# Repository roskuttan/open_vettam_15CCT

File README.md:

# open_vettam_15CCT

Tunable-white ceiling-light hardware project with a main control board and a
separate circular LED MCPCB.

## Current Hardware

### LED MCPCB

Verified from the current KiCad schematic and PCB:

- 130 mm circular board routed on `F.Cu`.
- 84 LEDs: 42 x `L128-5090HA35000K1` cool-white 5000 K and
  42 x `L128-3090HA35000K1` warm-white 3000 K.
- Six CW strings and six WW strings, each with a `6.8 ohm` resistor.
- LED power pads are `CW+`, `WW+`, and one shared `LED-`.
- The shared `LED-` pad connects to `GND0` used by both LED sheets.
- The three LED power wire pads are `3 x 6 mm`. The previous four separate
  power pads were `5 x 10 mm`.
- A `TMP112AIDRLR` temperature sensor is connected through `TEMP_3V3`,
  `TEMP_GND`, `TEMP_SCL`, and `TEMP_SDA` pads.

Sources:

- [`hardware/led-mcpcb/kicad/led_mcpcb.kicad_sch`](hardware/led-mcpcb/kicad/led_mcpcb.kicad_sch)
- [`hardware/led-mcpcb/kicad/led_mcpcb.kicad_pcb`](hardware/led-mcpcb/kicad/led_mcpcb.kicad_pcb)
- [`hardware/led-mcpcb/kicad/CW-5000.kicad_sch`](hardware/led-mcpcb/kicad/CW-5000.kicad_sch)
- [`hardware/led-mcpcb/kicad/WW-3000.kicad_sch`](hardware/led-mcpcb/kicad/WW-3000.kicad_sch)

### Main Board

Verified from the current KiCad schematic and PCB:

- 68.25 x 49 mm, two copper layers, fully routed.
- `24V` input with an `LMR51610YDBVR` buck regulator producing `3V3`.
- `ESP32-C6-MINI-1-N4` controller module.
- Two `TPS922053DRRR` LED drivers controlled by `PWM_CW` and `PWM_WW`.
- `LED_OUT` connector `J3` pinout:

| Pin | Current net |
|---:|---|
| 1 | `+24V` |
| 2 | `WW-` |
| 3 | `+24V` |
| 4 | `CW-` |

- `TEMP_IN` connector `J5` pinout:

| Pin | Current net |
|---:|---|
| 1 | `+3V3` |
| 2 | `GND` |
| 3 | `SCL` |
| 4 | `SDA` |

Sources:

- [`hardware/main-board/kicad/open_vettam_15CCT.kicad_sch`](hardware/main-board/kicad/open_vettam_15CCT.kicad_sch)
- [`hardware/main-board/kicad/open_vettam_15CCT.kicad_pcb`](hardware/main-board/kicad/open_vettam_15CCT.kicad_pcb)
- [`hardware/main-board/kicad/24v_Input.kicad_sch`](hardware/main-board/kicad/24v_Input.kicad_sch)
- [`hardware/main-board/kicad/24-5_buck.kicad_sch`](hardware/main-board/kicad/24-5_buck.kicad_sch)
- [`hardware/main-board/kicad/MCU.kicad_sch`](hardware/main-board/kicad/MCU.kicad_sch)
- [`hardware/main-board/kicad/cc_driver.kicad_sch`](hardware/main-board/kicad/cc_driver.kicad_sch)

## Interface Status

The current board files do not have matching LED power interfaces:

- The LED MCPCB uses `CW+`, `WW+`, and shared `LED-`.
- The main board still outputs `+24V`, `WW-`, `+24V`, and `CW-`.

The main-board LED-driver section must be revised before it can connect directly
to the current LED MCPCB interface.

## Repository Layout

```text
hardware/
  main-board/
    kicad/          Main-board KiCad source
    bom/            Main-board BOM export
    manufacturing/  Gerber ZIP, netlist, and stencil DXF files
  led-mcpcb/
    kicad/          LED-board KiCad source
    manufacturing/  LED-board stencil DXF
firmware/
  esp32-c6/         Firmware placeholder; no source code is present yet
docs/               Datasheets and manufacturing notes
cad/                Enclosure CAD
mechanical/         Mechanical models and assembly assets
```

Matter over Thread, CW/WW PWM, brightness control, and color-temperature control
are listed as planned firmware scope in
[`firmware/esp32-c6/README.md`](firmware/esp32-c6/README.md); they are not
implemented in this repository yet.

## License

- Hardware and CAD source: CERN-OHL-P-2.0
- Firmware and scripts: MIT
- Documentation and media: not licensed unless stated otherwise

See [`LICENSE`](LICENSE) and [`LICENSES/`](LICENSES/).

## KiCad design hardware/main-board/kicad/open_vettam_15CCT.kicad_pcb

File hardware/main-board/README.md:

# Main Board

Main ESP32-C6 control board.

- `kicad/`: KiCad schematic and PCB source
- `bom/`: BOM exports
- `manufacturing/`: fabrication, stencil, and netlist outputs

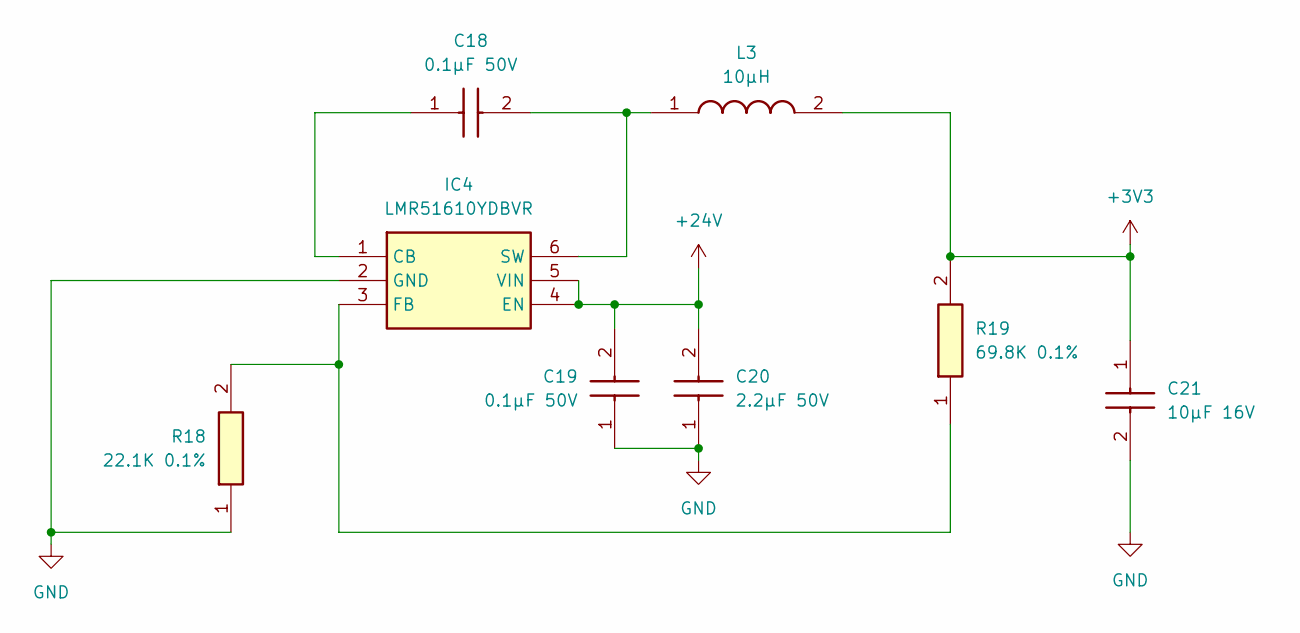
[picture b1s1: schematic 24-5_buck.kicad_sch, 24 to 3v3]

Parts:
C18, C19: 0.1µF 50V; CAPC1608X90N; Manufacturer_Part_Number CL10B104KB8NNNL; Mouser Part Number 187-CL10B104KB8NNNL
C20: 2.2µF 50V; CAPC3225X270N; Manufacturer_Part_Number CL32B225KBJNNNE; Mouser Part Number 187-CL32B225KBJNNNE
C21: 10µF 16V; CAPC3216X180N; Manufacturer_Part_Number C3216X7R1C106K160AC; Mouser Part Number 810-C3216X7R1C106K
IC4: LMR51610YDBVR; SOT95P280X145-6N; Manufacturer_Part_Number LMR51610YDBVR; Mouser Part Number 595-LMR51610YDBVR
L3: 10µH; SRP5030HMT2R2M; Manufacturer_Part_Number SRP5030HMT-100M; Mouser Part Number 652-SRP5030HMT-100M
R18: 22.1K 0.1%; ERA3AEB101V; Manufacturer_Part_Number ERA-3AEB2212V; Mouser Part Number 667-ERA-3AEB2212V
R19: 69.8K 0.1%; ERA3AEB101V; Manufacturer_Part_Number ERA-3AEB6982V; Mouser Part Number 667-ERA-3AEB6982V

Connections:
+3V3: C21.1, L3.2, R19.2; also elsewhere on the board
+24V: C19.2, C20.2, IC4.4 (EN), IC4.5 (VIN); also elsewhere on the board
GND: C19.1, C20.1, C21.2, IC4.2 (GND), R18.1; also elsewhere on the board
unnamed: C18.1, IC4.1 (CB)
unnamed: IC4.3 (FB), R18.2, R19.1
unnamed: C18.2, IC4.6 (SW), L3.1

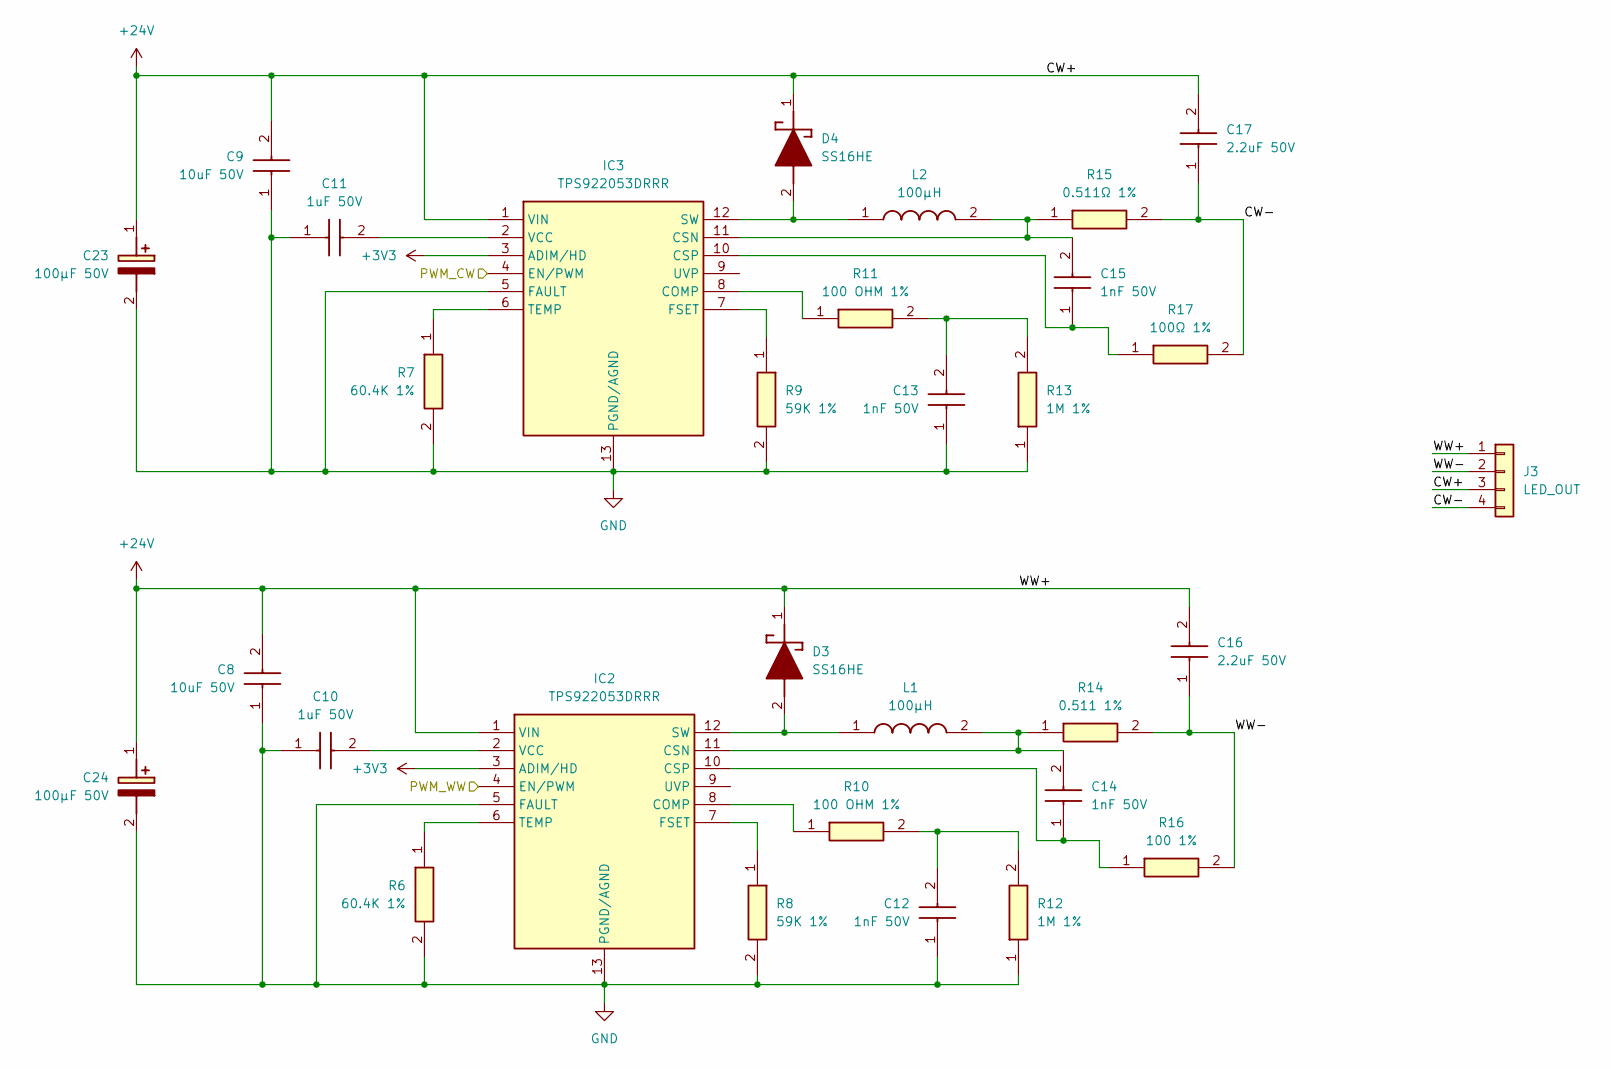
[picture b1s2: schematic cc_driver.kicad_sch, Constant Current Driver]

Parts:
C8, C9: 10uF 50V; CAPC3216X180N; Manufacturer_Part_Number CL31B106KBHNNNE; Mouser Part Number 187-CL31B106KBHNNNE
C10, C11: 1uF 50V; CAPC1608X95N; Manufacturer_Part_Number UMK107AB7105KA-T; Mouser Part Number 963-UMK107AB7105KA-T
C12, C13, C14, C15: 1nF 50V; CAPC1608X90N; Manufacturer_Part_Number CL10B102KB8NNNC; Mouser Part Number 187-CL10B102KB8NNNC
C16, C17: 2.2uF 50V; CAPC3216X180N; Manufacturer_Part_Number CL31B225KBHNNNE; Mouser Part Number 187-CL31B225KBHNNNE
C23, C24: 100µF 50V; CAPAE1030X1050N; Manufacturer_Part_Number 50THV100M10X10.5; Mouser Part Number 232-50THV100M10X10.5
D3, D4: SS16HE; Manufacturer_Part_Number SS16HE; Mouser Part Number 512-SS16HE
IC2, IC3: TPS922053DRRR; SON50P300X300X80-13N-D; Manufacturer_Part_Number TPS922053DRRR; Mouser Part Number 595-TPS922053DRRR
J3: LED_OUT; SolderWire-0.25sqmm_1x04_P4.5mm_D0.65mm_OD2mm
L1, L2: 100µH; AMDLA1004S101MT; Manufacturer_Part_Number AMDLA1004S-101MT; Mouser Part Number 815-AMDLA1004S-101MT
R6, R7: 60.4K 1%; RESC1608X55N; Manufacturer_Part_Number RC0603FR-0760K4L; Mouser Part Number 603-RC0603FR-0760K4L
R8, R9: 59K 1%; RESC1608X55N; Manufacturer_Part_Number RC0603FR-0759KL; Mouser Part Number 603-RC0603FR-0759KL
R10, R11: 100 OHM 1%; RESC1608X55N; Manufacturer_Part_Number RC0603FR-07100RL; Mouser Part Number 603-RC0603FR-07100RL
R12, R13: 1M 1%; RESC1608X55N; Manufacturer_Part_Number RC0603FR-071ML; Mouser Part Number 603-RC0603FR-071ML
R14: 0.511 1%; RESC3216X70N; Manufacturer_Part_Number SR732BTTDR511F; Mouser Part Number 660-SR732BTTER511F
R15: 0.511Ω 1%; RESC3216X70N; Manufacturer_Part_Number SR732BTTDR511F; Mouser Part Number 660-SR732BTTER511F
R16: 100 1%; RESC1608X55N; Manufacturer_Part_Number RC0603FR-07100RL; Mouser Part Number 603-RC0603FR-07100RL
R17: 100Ω 1%; RESC1608X55N; Manufacturer_Part_Number RC0603FR-07100RL; Mouser Part Number 603-RC0603FR-07100RL

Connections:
+3V3: IC2.3 (ADIM/HD), IC3.3 (ADIM/HD); also elsewhere on the board
+24V: C8.2, C9.2, C16.2, C17.2, C23.1 (+), C24.1 (+), D3.1 (K), D4.1 (K), IC2.1 (VIN), IC3.1 (VIN), J3.1, J3.3; also elsewhere on the board
/CC_Driver/CW-: C17.1, J3.4, R15.2, R17.2
/CC_Driver/PWM_CW: IC3.4 (EN/PWM); also elsewhere on the board
/CC_Driver/PWM_WW: IC2.4 (EN/PWM); also elsewhere on the board
/CC_Driver/WW-: C16.1, J3.2, R14.2, R16.2
GND: C8.1, C9.1, C10.1, C11.1, C12.1, C13.1, C23.2 (-), C24.2 (-), IC2.5 (FAULT), IC2.13 (PGND/AGND), IC3.5 (FAULT), IC3.13 (PGND/AGND), R6.2, R7.2, R8.2, R9.2, R12.1, R13.1; also elsewhere on the board
unnamed: C12.2, R10.2, R12.2
unnamed: C13.2, R11.2, R13.2
unnamed: D3.2 (A), IC2.12 (SW), L1.1
unnamed: D4.2 (A), IC3.12 (SW), L2.1
unnamed: IC2.8 (COMP), R10.1
unnamed: C14.2, IC2.11 (CSN), L1.2, R14.1
unnamed: C14.1, IC2.10 (CSP), R16.1
unnamed: IC2.7 (FSET), R8.1
unnamed: IC2.6 (TEMP), R6.1
unnamed: C10.2, IC2.2 (VCC)
unnamed: IC3.8 (COMP), R11.1
unnamed: C15.2, IC3.11 (CSN), L2.2, R15.1
unnamed: C15.1, IC3.10 (CSP), R17.1
unnamed: IC3.7 (FSET), R9.1
unnamed: IC3.6 (TEMP), R7.1
unnamed: C11.2, IC3.2 (VCC)

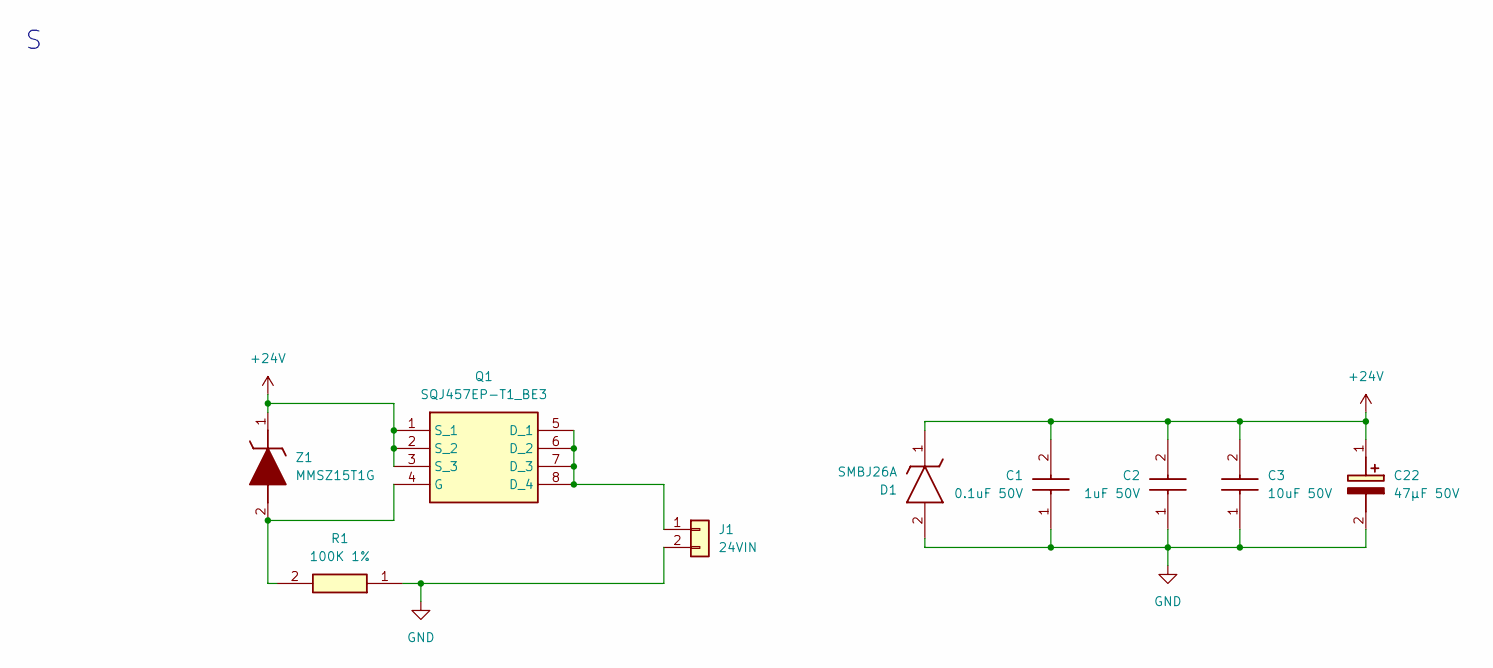
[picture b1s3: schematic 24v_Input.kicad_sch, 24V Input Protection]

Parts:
C1: 0.1uF 50V; CAPC1608X90N; Manufacturer_Part_Number CL10B104KB8NNWC; Mouser Part Number 187-CL10B104KB8NNWC
C2: 1uF 50V; CAPC1608X95N; Manufacturer_Part_Number UMK107AB7105KA-T; Mouser Part Number 963-UMK107AB7105KA-T
C3: 10uF 50V; CAPC3216X180N; Manufacturer_Part_Number CL31B106KBHNNNE; Mouser Part Number 187-CL31B106KBHNNNE
C22: 47µF 50V; CAPAE830X1050N; Manufacturer_Part_Number HHXC500ARA470MHA0G; Mouser Part Number 661-HHXC500A470MHA0G
D1: SMBJ26A; DIOM5436X261N; Manufacturer_Part_Number SMBJ26A; Mouser Part Number 576-SMBJ26A
J1: 24VIN; SolderWire-0.15sqmm_1x06_P4mm_D0.5mm_OD1.5mm
Q1: SQJ457EP-T1_BE3; SQJ416EPT1_GE3; Manufacturer_Part_Number SQJ457EP-T1_BE3; Mouser Part Number 78-SQJ457EP-T1_BE3
R1: 100K 1%; RESC1608X55N; Manufacturer_Part_Number RC0603FR-07100KL; Mouser Part Number 603-RC0603FR-07100KL
Z1: MMSZ15T1G; DIOM3716X135N; Manufacturer_Part_Number MMSZ15T1G; Mouser Part Number 863-MMSZ15T1G

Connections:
+24V: C1.2, C2.2, C3.2, C22.1 (+), D1.1 (K), Q1.1 (S_1), Q1.2 (S_2), Q1.3 (S_3), Z1.1 (K); also elsewhere on the board
GND: C1.1, C2.1, C3.1, C22.2 (-), D1.2 (A), J1.2, R1.1; also elsewhere on the board
unnamed: J1.1, Q1.5 (D_1), Q1.6 (D_2), Q1.7 (D_3), Q1.8 (D_4)
unnamed: Q1.4 (G), R1.2, Z1.2 (A)

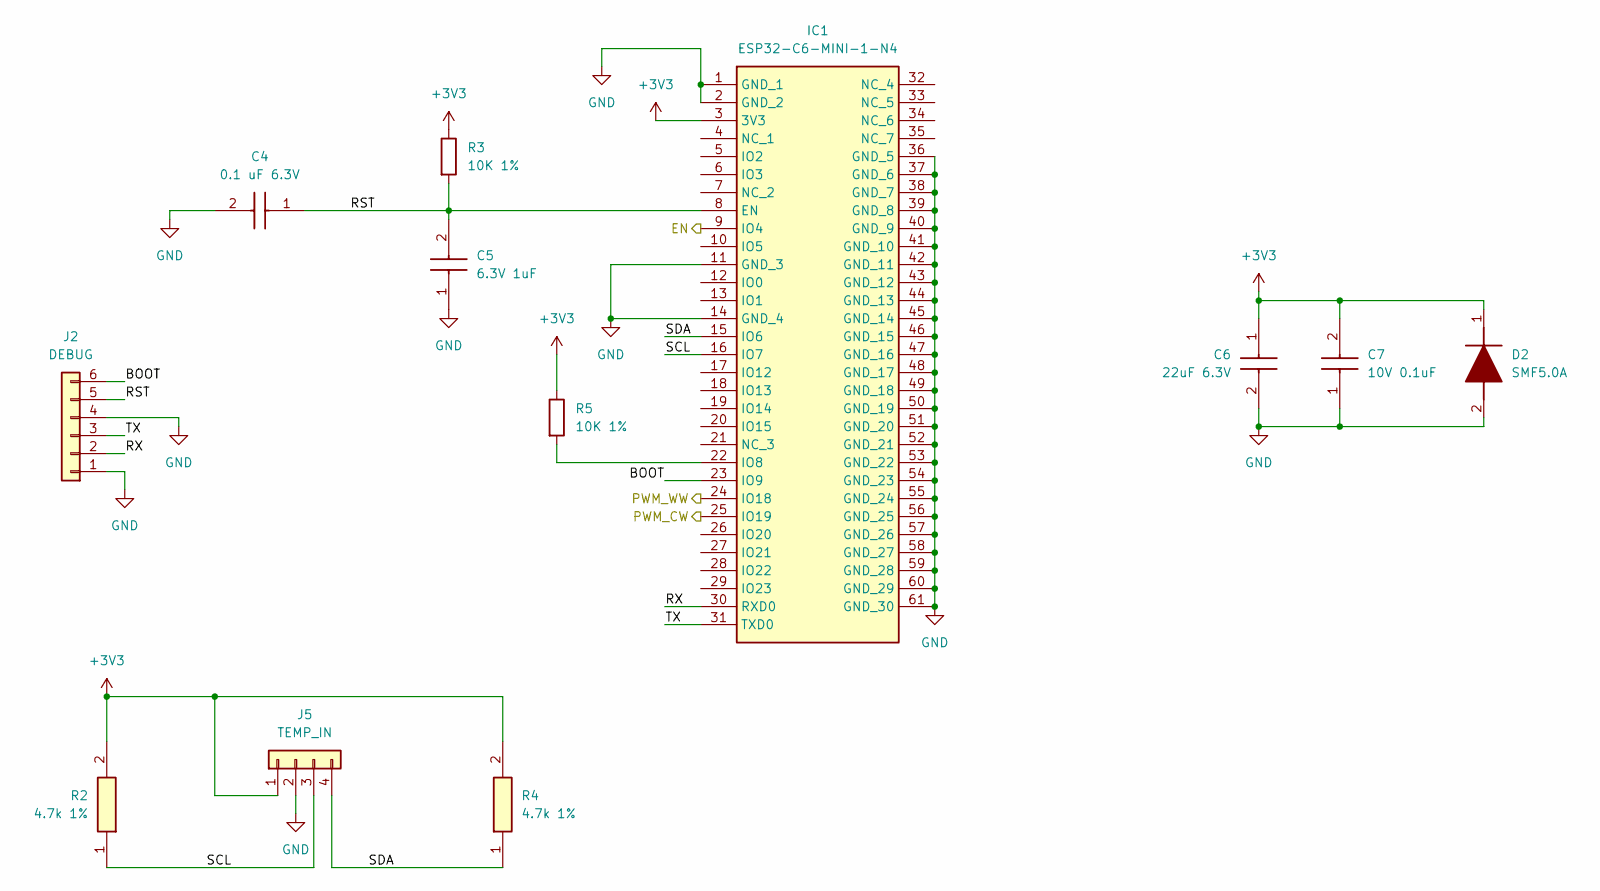
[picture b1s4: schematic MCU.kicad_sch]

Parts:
C4: 0.1 uF 6.3V; C0603; Manufacturer_Part_Number C0603C104K9PACTU; Mouser Part Number 80-C0603C104K9P
C5: 6.3V 1uF; CAPC1608X90N; Manufacturer_Part_Number CL10B105KQ8NNNC; Mouser Part Number 187-CL10B105KQ8NNNC
C6: 22uF 6.3V; CAPC1608X100N; Manufacturer_Part_Number CL10A226MQ8NRNE; Mouser Part Number 187-CL10A226MQ8NRNE
C7: 10V 0.1uF; C0402; Manufacturer_Part_Number C0402C104K8RACAUTO; Mouser Part Number 80-C0402C104K8RAUTO
D2: SMF5.0A; SODFL3618X110N; Manufacturer_Part_Number SMF5.0A; Mouser Part Number 576-SMF5.0A
IC1: ESP32-C6-MINI-1-N4; ESP32C6MINI1N4; Manufacturer_Part_Number ESP32-C6-MINI-1-N4; Mouser Part Number 356-ESP32C6MINI-1-N4
J2: DEBUG; SolderWire-0.15sqmm_1x06_P4mm_D0.5mm_OD1.5mm
J5: TEMP_IN; SolderWire-0.15sqmm_1x04_P4mm_D0.5mm_OD1.5mm
R2, R4: 4.7k 1%; RESC1608X55N; Manufacturer_Part_Number ERJ-3EKF4701V; Mouser Part Number 667-ERJ-3EKF4701V
R3, R5: 10K 1%; R_0603_1608Metric_Pad0.98x0.95mm_HandSolder; Manufacturer_Part_Number RC0603FR-0710KL; Mouser Part Number 603-RC0603FR-0710KL

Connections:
+3V3: C6.1, C7.2, D2.1 (K), IC1.3 (3V3), J5.1, R2.2, R3.1, R4.2, R5.1; also elsewhere on the board
/MCU/<NO NET>: IC1.23 (IO9), J2.6; also elsewhere on the board
/MCU/RST: C4.1, C5.2, IC1.8 (EN), J2.5, R3.2; also elsewhere on the board
/MCU/RX: IC1.30 (RXD0), J2.2; also elsewhere on the board
/MCU/SCL: IC1.16 (IO7), J5.3, R2.1; also elsewhere on the board
/MCU/SDA: IC1.15 (IO6), J5.4, R4.1; also elsewhere on the board
/MCU/TX: IC1.31 (TXD0), J2.3; also elsewhere on the board
GND: C4.2, C5.1, C6.2, C7.1, D2.2 (A), IC1.1 (GND_1), IC1.2 (GND_2), IC1.11 (GND_3), IC1.14 (GND_4), IC1.36 (GND_5), IC1.37 (GND_6), IC1.38 (GND_7), IC1.39 (GND_8), IC1.40 (GND_9), IC1.41 (GND_10), IC1.42 (GND_11), IC1.43 (GND_12), IC1.44 (GND_13), IC1.45 (GND_14), IC1.46 (GND_15), IC1.47 (GND_16), IC1.48 (GND_17), IC1.49 (GND_18), IC1.50 (GND_19), IC1.51 (GND_20), IC1.52 (GND_21), IC1.53 (GND_22), IC1.54 (GND_23), IC1.55 (GND_24), IC1.56 (GND_25), IC1.57 (GND_26), IC1.58 (GND_27), IC1.59 (GND_28), IC1.60 (GND_29), IC1.61 (GND_30), J2.1, J2.4, J5.2; also elsewhere on the board
unnamed 18: IC1.22 (IO8), R5.2; also elsewhere on the board

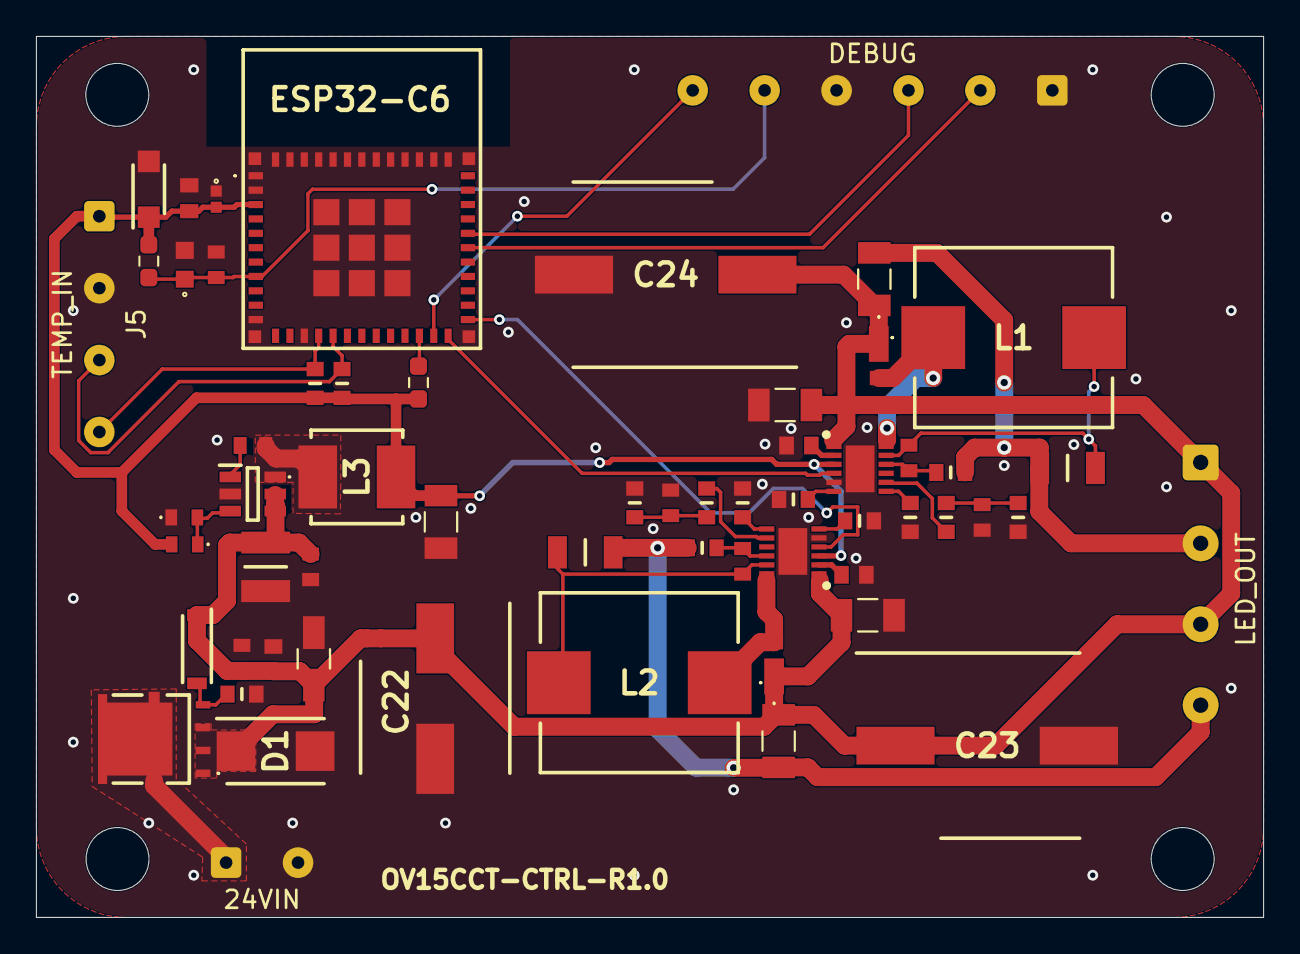
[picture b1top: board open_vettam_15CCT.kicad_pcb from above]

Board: 2 copper layers, 68.2 x 49.0 mm, 60 parts (0 on the bottom side), 35 nets.

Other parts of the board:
ESP32-C6: ESP32-C6-MINI-1-N4; ESP32C6MINI1N4

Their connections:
+3V3: ESP32-C6.3 (3V3); also elsewhere on the board
/CC_Driver/PWM_CW: ESP32-C6.25 (IO19); also elsewhere on the board
/CC_Driver/PWM_WW: ESP32-C6.24 (IO18); also elsewhere on the board
/MCU/<NO NET>: ESP32-C6.23 (IO9); also elsewhere on the board
/MCU/RST: ESP32-C6.8 (EN); also elsewhere on the board
/MCU/RX: ESP32-C6.30 (RXD0); also elsewhere on the board
/MCU/SCL: ESP32-C6.16 (IO7); also elsewhere on the board
/MCU/SDA: ESP32-C6.15 (IO6); also elsewhere on the board
/MCU/TX: ESP32-C6.31 (TXD0); also elsewhere on the board
GND: ESP32-C6.1 (GND_1), ESP32-C6.2 (GND_2), ESP32-C6.11 (GND_3), ESP32-C6.14 (GND_4), ESP32-C6.36 (GND_5), ESP32-C6.37 (GND_6), ESP32-C6.38 (GND_7), ESP32-C6.39 (GND_8), ESP32-C6.40 (GND_9), ESP32-C6.41 (GND_10), ESP32-C6.42 (GND_11), ESP32-C6.43 (GND_12), ESP32-C6.44 (GND_13), ESP32-C6.45 (GND_14), ESP32-C6.46 (GND_15), ESP32-C6.47 (GND_16), ESP32-C6.48 (GND_17), ESP32-C6.49 (GND_18), ESP32-C6.50 (GND_19), ESP32-C6.51 (GND_20), ESP32-C6.52 (GND_21), ESP32-C6.53 (GND_22), ESP32-C6.54 (GND_23), ESP32-C6.55 (GND_24), ESP32-C6.56 (GND_25), ESP32-C6.57 (GND_26), ESP32-C6.58 (GND_27), ESP32-C6.59 (GND_28), ESP32-C6.60 (GND_29), ESP32-C6.61 (GND_30); also elsewhere on the board
unnamed 18: ESP32-C6.22 (IO8); also elsewhere on the board

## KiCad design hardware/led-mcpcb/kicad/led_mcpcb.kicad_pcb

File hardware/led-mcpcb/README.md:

# LED MCPCB

Metal-core LED board for the CW and WW LED strings.

- `kicad/`: KiCad schematic, PCB, and design rules
- `tools/`: placement helper files

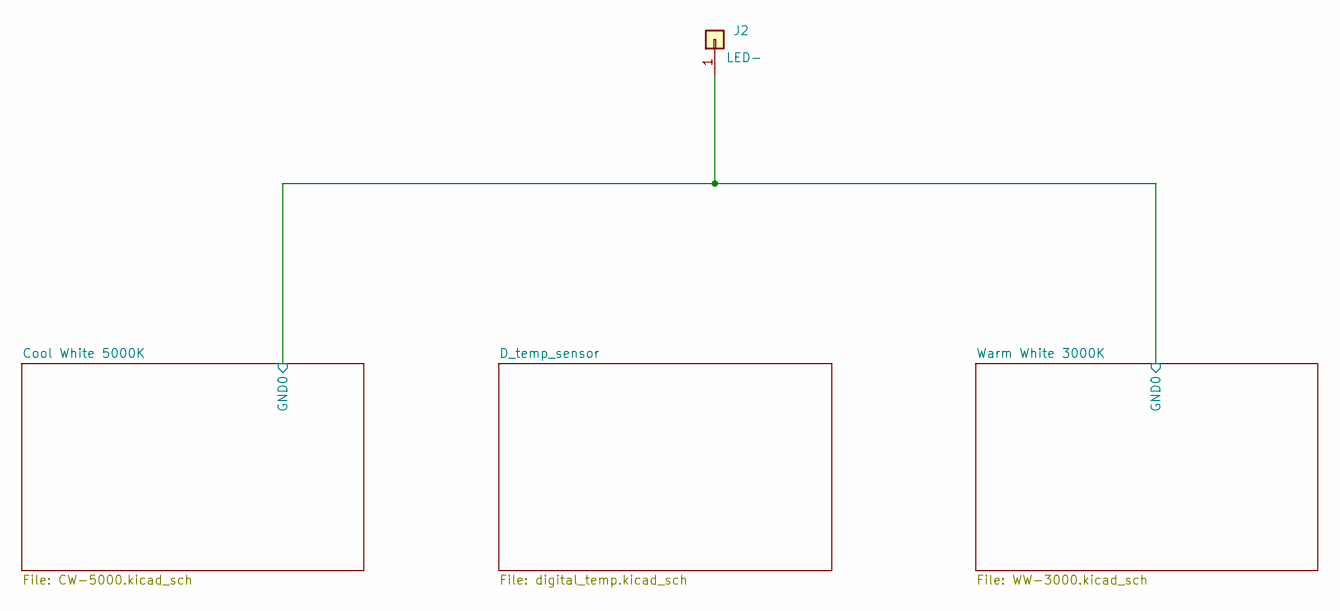
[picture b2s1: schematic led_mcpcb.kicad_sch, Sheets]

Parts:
J2: LED-; SolderWirePad_1x01_SMD_3x6mm

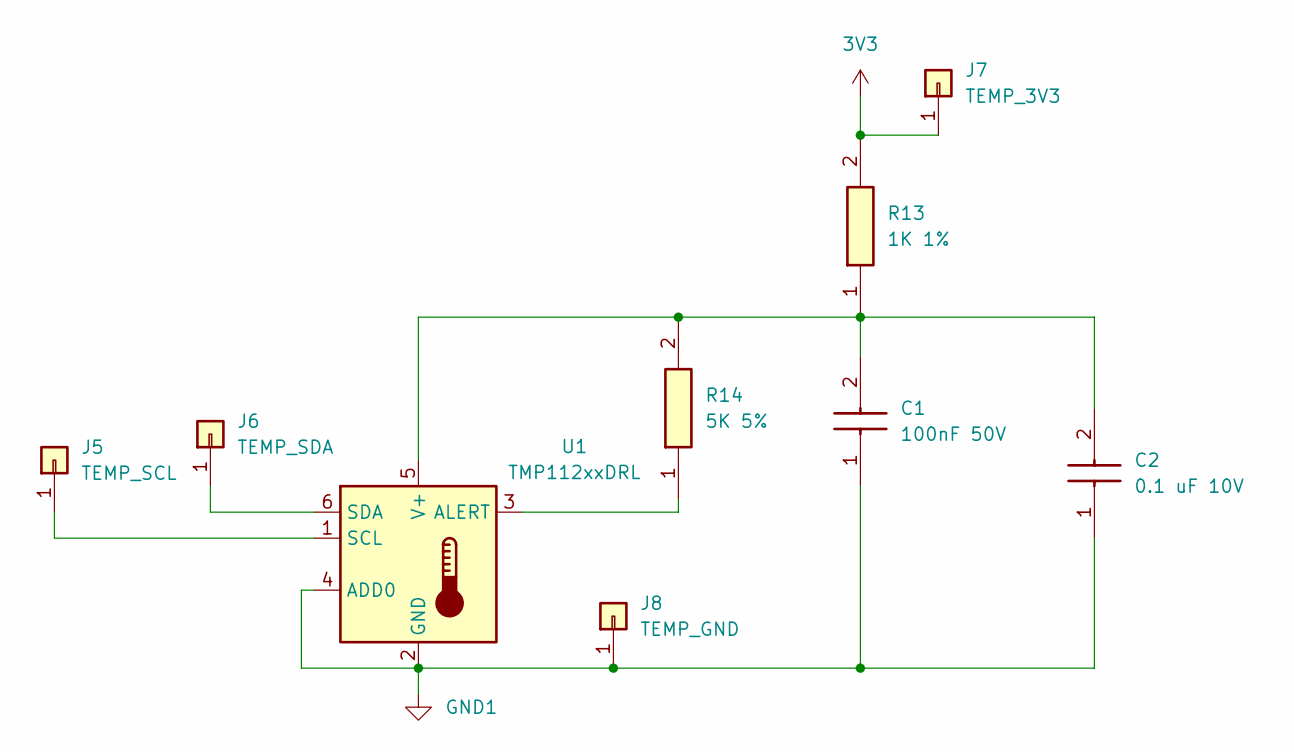
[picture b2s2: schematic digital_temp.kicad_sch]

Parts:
C1: 100nF 50V; CAPC1608X90N; Manufacturer_Part_Number CL10B104KB8NNNL; Mouser Part Number 187-CL10B104KB8NNNL
C2: 0.1 uF 10V; C0402; Manufacturer_Part_Number C0402C104K8RACAUTO; Mouser Part Number 80-C0402C104K8RAUTO
J5: TEMP_SCL; SolderWirePad_1x01_SMD_1x2mm
J6: TEMP_SDA; SolderWirePad_1x01_SMD_1x2mm
J7: TEMP_3V3; SolderWirePad_1x01_SMD_1x2mm
J8: TEMP_GND; SolderWirePad_1x01_SMD_1x2mm
R13: 1K 1%; RESC1608X55N; Manufacturer_Part_Number ERJ-3EKF1001V; Mouser Part Number 667-ERJ-3EKF1001V
R14: 5K 5%; RESC2012X50N; Manufacturer_Part_Number CRCW08055K00JNTA; Mouser Part Number 71-CRCW0805J-5K
U1: TMP112xxDRL; SOT-563; Manufacturer_Part_Number TMP112AIDRLR; Mouser Part Number 595-TMP112AIDRLR

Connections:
3V3: J7.1 (Pin_1_1), R13.2
GND1: C1.1, C2.1, J8.1 (Pin_1_1), U1.2 (GND), U1.4 (ADD0)
unnamed: J5.1 (Pin_1_1), U1.1 (SCL)
unnamed: J6.1 (Pin_1_1), U1.6 (SDA)
unnamed: R14.1, U1.3 (ALERT)
unnamed: C1.2, C2.2, R13.1, R14.2, U1.5 (V+)

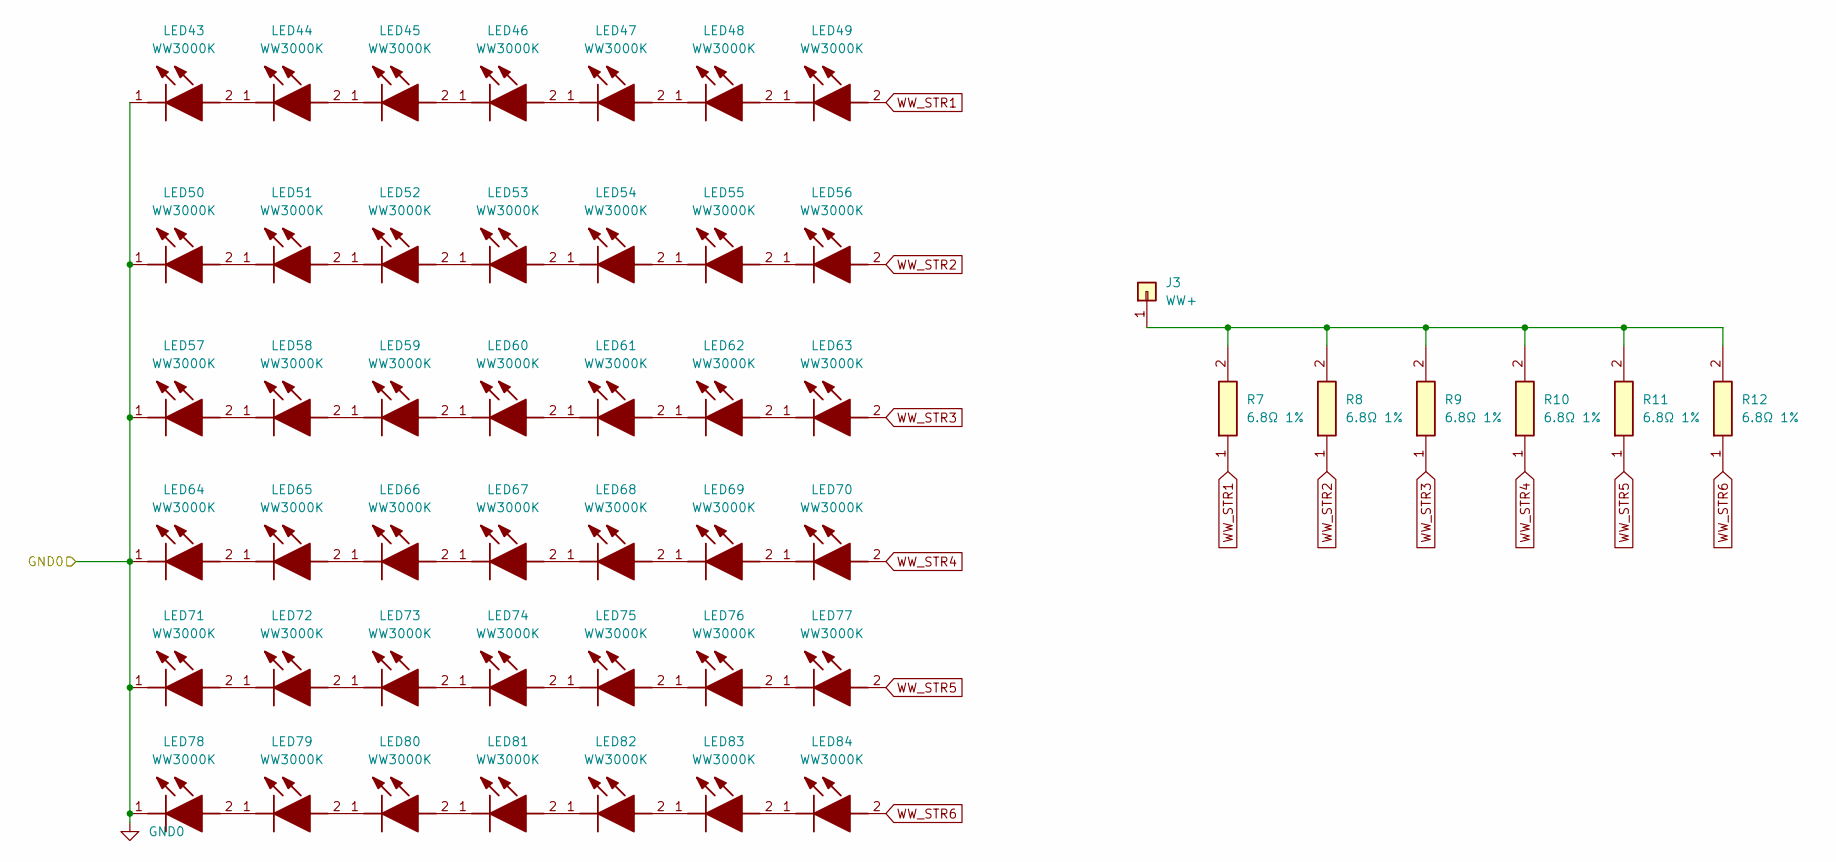
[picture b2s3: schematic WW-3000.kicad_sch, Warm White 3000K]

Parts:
J3: WW+; SolderWirePad_1x01_SMD_3x6mm
LED43, LED44, LED45, LED46, LED47, LED48, LED49, LED50, LED51, LED52, LED53, LED55, LED56, LED57, LED58, LED59, LED60, LED62, LED63, LED64, LED65, LED66, LED67, LED68, LED69, LED70, LED71, LED72, LED73, LED74, LED75, LED76, LED77, LED78, LED79, LED80, LED81, LED82, LED83, LED84: WW3000K; L1283090HA35000K1; Manufacturer_Part_Number L128-3090HA35000K1; Mouser Part Number 997-L1283090HA3500K1
LED54, LED61: WW3000K; L1285090HA35000K1; Manufacturer_Part_Number L128-3090HA35000K1; Mouser Part Number 997-L1283090HA3500K1
R7, R8, R9, R10, R11, R12: 6.8Ω 1%; RESC3116X65N; Manufacturer_Part_Number RC1206FR-076R8L; Mouser Part Number 603-RC1206FR-076R8L

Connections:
GND0: LED43.1 (K), LED50.1 (K), LED57.1 (K), LED64.1 (K), LED71.1 (K), LED78.1 (K); also elsewhere on the board
unnamed 10: J3.1, R7.2, R8.2, R9.2, R10.2, R11.2, R12.2; also elsewhere on the board
unnamed: LED43.2 (A), LED44.1 (K)
unnamed: LED44.2 (A), LED45.1 (K)
unnamed: LED45.2 (A), LED46.1 (K)
unnamed: LED46.2 (A), LED47.1 (K)
unnamed: LED47.2 (A), LED48.1 (K)
unnamed: LED48.2 (A), LED49.1 (K)
unnamed: LED50.2 (A), LED51.1 (K)
unnamed: LED51.2 (A), LED52.1 (K)
unnamed: LED52.2 (A), LED53.1 (K)
unnamed: LED53.2 (A), LED54.1 (K)
unnamed: LED54.2 (A), LED55.1 (K)
unnamed: LED55.2 (A), LED56.1 (K)
unnamed: LED57.2 (A), LED58.1 (K)
unnamed: LED58.2 (A), LED59.1 (K)
unnamed: LED59.2 (A), LED60.1 (K)
unnamed: LED60.2 (A), LED61.1 (K)
unnamed: LED61.2 (A), LED62.1 (K)
unnamed: LED62.2 (A), LED63.1 (K)
unnamed: LED64.2 (A), LED65.1 (K)
unnamed: LED65.2 (A), LED66.1 (K)
unnamed: LED66.2 (A), LED67.1 (K)
unnamed: LED67.2 (A), LED68.1 (K)
unnamed: LED68.2 (A), LED69.1 (K)
unnamed: LED69.2 (A), LED70.1 (K)
unnamed: LED71.2 (A), LED72.1 (K)
unnamed: LED72.2 (A), LED73.1 (K)
unnamed: LED73.2 (A), LED74.1 (K)
unnamed: LED74.2 (A), LED75.1 (K)
unnamed: LED75.2 (A), LED76.1 (K)
unnamed: LED76.2 (A), LED77.1 (K)
unnamed: LED78.2 (A), LED79.1 (K)
unnamed: LED79.2 (A), LED80.1 (K)
unnamed: LED80.2 (A), LED81.1 (K)
unnamed: LED81.2 (A), LED82.1 (K)
unnamed: LED82.2 (A), LED83.1 (K)
unnamed: LED83.2 (A), LED84.1 (K)
WW_STR1: LED49.2 (A), R7.1
WW_STR2: LED56.2 (A), R8.1
WW_STR3: LED63.2 (A), R9.1
WW_STR4: LED70.2 (A), R10.1
WW_STR5: LED77.2 (A), R11.1
WW_STR6: LED84.2 (A), R12.1

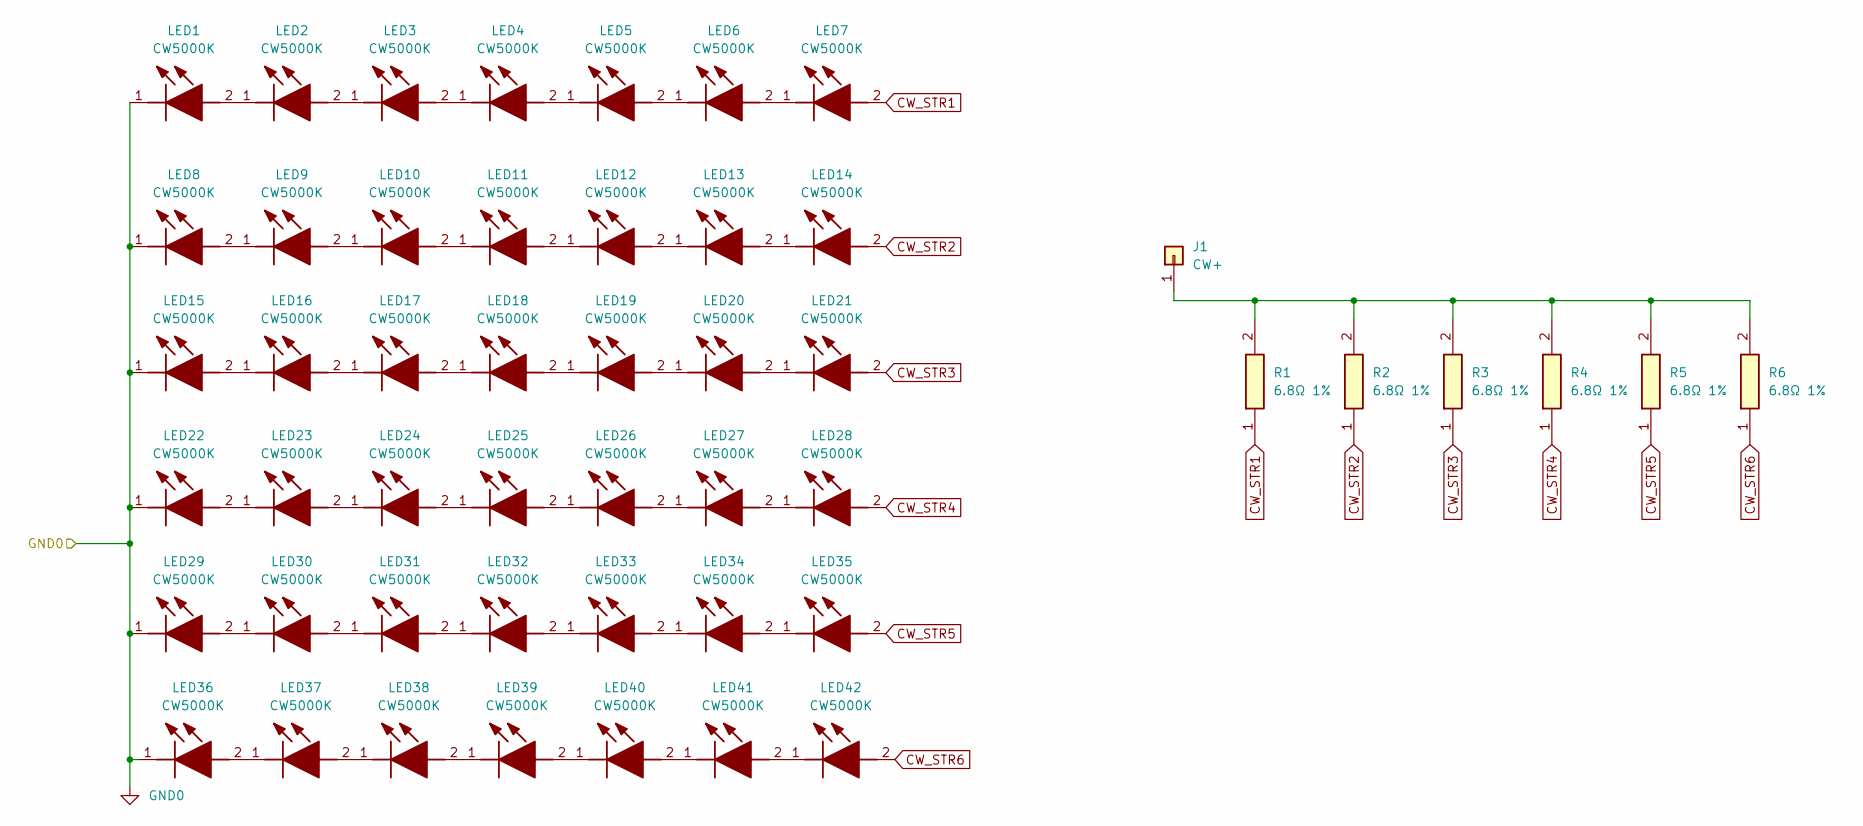
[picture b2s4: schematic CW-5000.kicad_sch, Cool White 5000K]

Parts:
J1: CW+; SolderWirePad_1x01_SMD_3x6mm
LED1, LED2, LED3, LED4, LED5, LED6, LED7, LED8, LED9, LED10, LED11, LED12, LED13, LED14, LED15, LED16, LED17, LED18, LED19, LED20, LED21, LED22, LED23, LED24, LED25, LED26, LED27, LED28, LED29, LED30, LED31, LED32, LED33, LED34, LED35, LED36, LED37, LED38, LED39, LED40, LED41, LED42: CW5000K; L1283090HA35000K1; Manufacturer_Part_Number L128-5090HA35000K1; Mouser Part Number 997-L1285090HA3500K1
R1, R2, R3, R4, R5, R6: 6.8Ω 1%; RESC3116X65N; Manufacturer_Part_Number RC1206FR-076R8L; Mouser Part Number 603-RC1206FR-076R8L

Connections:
CW_STR1: LED7.2 (A), R1.1
CW_STR2: LED14.2 (A), R2.1
CW_STR3: LED21.2 (A), R3.1
CW_STR4: LED28.2 (A), R4.1
CW_STR5: LED35.2 (A), R5.1
CW_STR6: LED42.2 (A), R6.1
GND0: LED1.1 (K), LED8.1 (K), LED15.1 (K), LED22.1 (K), LED29.1 (K), LED36.1 (K); also elsewhere on the board
unnamed 9: J1.1, R1.2, R2.2, R3.2, R4.2, R5.2, R6.2; also elsewhere on the board
unnamed: LED1.2 (A), LED2.1 (K)
unnamed: LED2.2 (A), LED3.1 (K)
unnamed: LED3.2 (A), LED4.1 (K)
unnamed: LED4.2 (A), LED5.1 (K)
unnamed: LED5.2 (A), LED6.1 (K)
unnamed: LED6.2 (A), LED7.1 (K)
unnamed: LED8.2 (A), LED9.1 (K)
unnamed: LED10.2 (A), LED11.1 (K)
unnamed: LED9.2 (A), LED10.1 (K)
unnamed: LED11.2 (A), LED12.1 (K)
unnamed: LED12.2 (A), LED13.1 (K)
unnamed: LED13.2 (A), LED14.1 (K)
unnamed: LED15.2 (A), LED16.1 (K)
unnamed: LED16.2 (A), LED17.1 (K)
unnamed: LED17.2 (A), LED18.1 (K)
unnamed: LED18.2 (A), LED19.1 (K)
unnamed: LED19.2 (A), LED20.1 (K)
unnamed: LED20.2 (A), LED21.1 (K)
unnamed: LED22.2 (A), LED23.1 (K)
unnamed: LED23.2 (A), LED24.1 (K)
unnamed: LED24.2 (A), LED25.1 (K)
unnamed: LED25.2 (A), LED26.1 (K)
unnamed: LED26.2 (A), LED27.1 (K)
unnamed: LED27.2 (A), LED28.1 (K)
unnamed: LED29.2 (A), LED30.1 (K)
unnamed: LED30.2 (A), LED31.1 (K)
unnamed: LED31.2 (A), LED32.1 (K)
unnamed: LED32.2 (A), LED33.1 (K)
unnamed: LED33.2 (A), LED34.1 (K)
unnamed: LED34.2 (A), LED35.1 (K)
unnamed: LED36.2 (A), LED37.1 (K)
unnamed: LED37.2 (A), LED38.1 (K)
unnamed: LED38.2 (A), LED39.1 (K)
unnamed: LED39.2 (A), LED40.1 (K)
unnamed: LED40.2 (A), LED41.1 (K)
unnamed: LED41.2 (A), LED42.1 (K)
